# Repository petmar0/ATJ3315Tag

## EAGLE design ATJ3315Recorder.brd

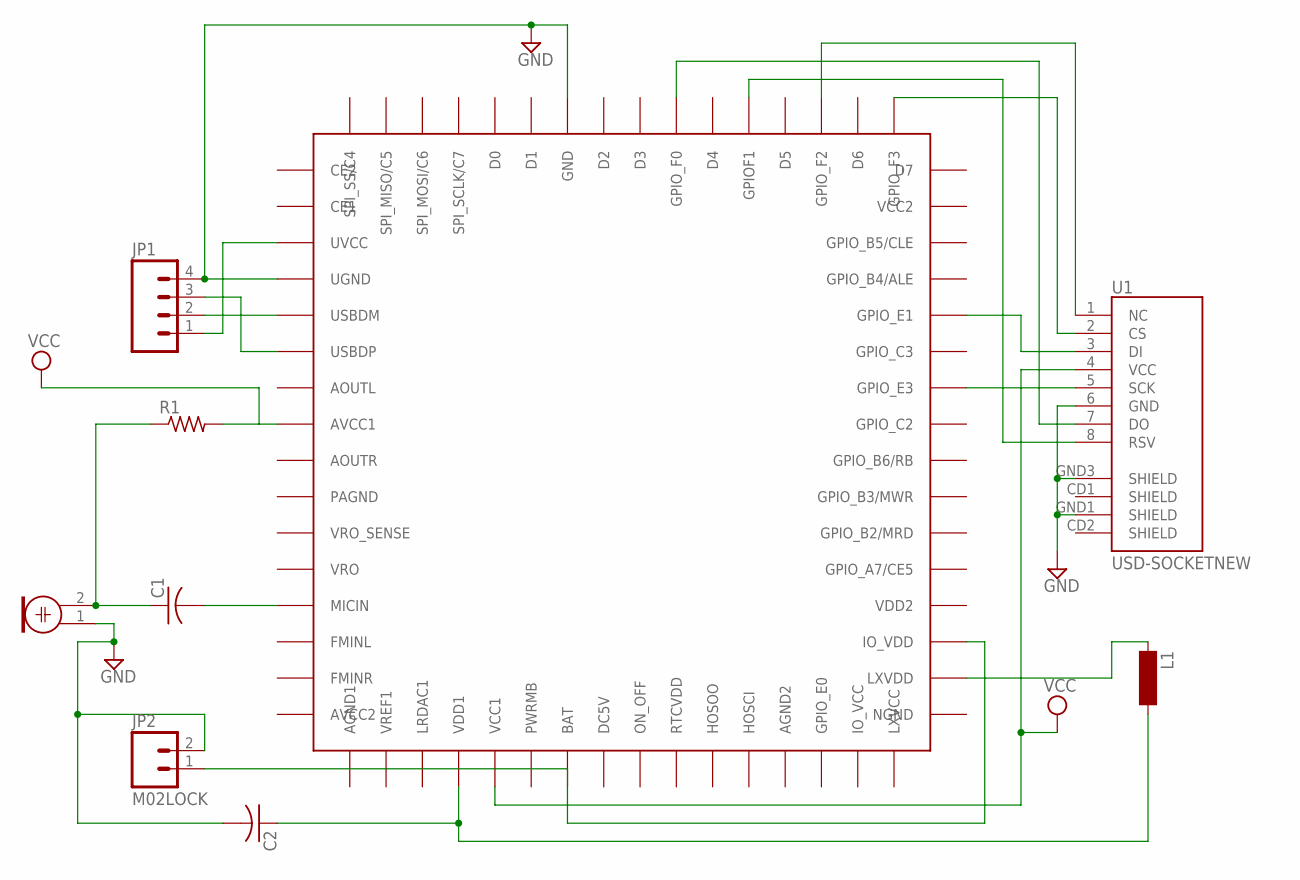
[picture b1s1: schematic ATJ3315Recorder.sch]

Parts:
C1, C2: C-USC0201; C0201
JP1: M04PTH; 1X04
JP2: M02LOCK; 1X02_LOCK
L1: SM-1206
M1: ELECTRET_MICROPHON-WM-61A; WM-61A
R1: R-US_M0805; M0805
U1: USD-SOCKETNEW; MICRO-SD-SOCKET-PP
U$4: AJ3315; 64M1

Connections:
GND: C2.2, JP1.4, JP2.2, M1.1, U1.6 (GND), U1.GND1 (SHIELD), U1.GND3 (SHIELD), U$4.4 (UGND), U$4.58 (GND)
unnamed: JP1.2, U$4.5 (USBDM)
unnamed: JP1.3, U$4.6 (USBDP)
unnamed: JP2.1, U$4.23 (BAT), U$4.35 (IO_VDD)
unnamed: JP1.1, U$4.3 (UVCC)
unnamed: R1.2, U$4.8 (AVCC1)
unnamed: C1.1, M1.2, R1.1
unnamed: C1.2, U$4.13 (MICIN)
unnamed: U1.5 (SCK), U$4.42 (GPIO_E3)
unnamed: U1.7 (DO), U$4.55 (GPIO_F0)
unnamed: U1.1 (NC), U$4.51 (GPIO_F2)
unnamed: U1.2 (CS), U$4.49 (GPIO_F3)
unnamed: U1.3 (DI), U$4.44 (GPIO_E1)
unnamed: U1.8 (RSV), U$4.53 (GPIOF1)
unnamed: L1.1, U$4.34 (LXVDD)
unnamed: C2.1, L1.2, U$4.20 (VDD1)
VCC: U1.4 (VCC), U$4.21 (VCC1)

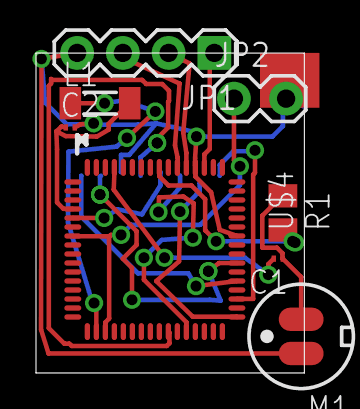
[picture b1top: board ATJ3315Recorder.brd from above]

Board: 2 copper layers, 14.9 x 17.8 mm, 9 parts (1 on the bottom side), 17 nets.

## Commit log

2015-02-17 Made PDFs

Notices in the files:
parts and their libraries:
SparkFun-Connectors: Licensing: CC v3.0 Share-Alike You are welcome to use this library for commercial purposes.
